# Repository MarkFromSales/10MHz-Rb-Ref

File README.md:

# 10MHz-Rb-Ref
Working on a custom controller for a 10MHz frequency reference

This sort of thing is fairly well documented in other places, but I wanted to use this as a way to learn. Most of my equipment has 10MHz frequency external reference capability and, although I don't really need it today, I'd like to learn more about the technology in general how it's used in instruments.

eBay often has 10MHz frequency references as components pulled out of telecom or similar equipment. After some quick searching I found that Rubidium is listed s one of the most stable and common references available. I bought an Efratom Rb 10MHz oscillator and this build log is to track efforts associated with getting it working.

I couldn't find much direct correlation between the device, its labels, and documentation. The FRS manual and pinouts accurately describe the device and its behavior, so I'm assuming I've got this correct so far :)

The connector that came with it was a pin type rather than solder cup. The heat from the soldering appeared to have weakened the pins resulting in some breakage on pin 1, causing issues with my testing.

Materials so far
* Efratom Rubidium Oscillator (eBay)
* ITT Cannon DAM11W1S connector (Digi-Key IDAM11W1S-ND)
* ITT Cannon DM53740-5008 coax pin (Digi-Key DM53740-5008PG-ND) - this turned out to be too small for my coax
* ITT Cannon DM53740-5002 coax pin (Digi-Key IDM53740-5002-ND)  - larger diameter on the coax side
* Amphenol 031-4803-RFX BNC panel adapter (Digi-Key ARF1685-ND)
* Amphenol 115101-01-06.00 BNC RG-316 cable in 6" length
* Mean Well IRM-60-24ST 24V 2.5A 60W AC-DC converter (Digi-Key 1866-3068-ND)

Efratom FRS Manual
https://s3.amazonaws.com/markfromsales/10mhzreference/Efratom_FRS_Manual.pdf

Efratom FRS Pinouts
https://s3.amazonaws.com/markfromsales/10mhzreference/Efratom_Pinouts.PNG

My unit's label
https://s3.amazonaws.com/markfromsales/10mhzreference/Efratom_Label.png

Screenshot of waveform (square, sort of)
https://s3.amazonaws.com/markfromsales/10mhzreference/Efratom_Waveform_20181114_1845.png

After reading through the documentation it looks like pins 1, 4, and 7 are not for customer use and there is some intersting items in the documentation. I connected them to my DAQ and ran a 60-minute capture from power-on to see what happened.

The documentation says that at power on the unit provides 10MHz via a crystal for about 4-minutes until the Rb lamp heats up. After the Rb lamp is heated it'll switch to Rb instead of crystal. This can be monitored by looking at the "Lock" pin 1 voltage; ~5V (mean is 5.1) is crystal and ~0V is Rb.

Check out the chart,
https://s3.amazonaws.com/markfromsales/10mhzreference/Efratom_Testing_Run_20181114_1840.PNG

It's very clear on my Siglent SDG 2042X counter function that the crystal is quite accurate and fairly stable, whereas the Rb is dead-on 10MHz and extremely stable.

Power draw is >1250mA while crystal is running and lamp is warming, drops down to 300-400mA after Rb locks. I was using Eevblog's uCurrent for this with a 3V battery. I've since soldered in an external battery connector and will use a 5V source from now on

Next steps:
* Re-run tests with a 5V power source in my uCurrent (3V current reading max is 1250mA) or run through DMM
* Package unit in metal box with appropriate PSU and cooling: Learn high-level thermal design principles
* Signal quality causes and does it matter? Learn high-level RF stuff and associated details
* Discover value of a frequency standard in my lab and projects

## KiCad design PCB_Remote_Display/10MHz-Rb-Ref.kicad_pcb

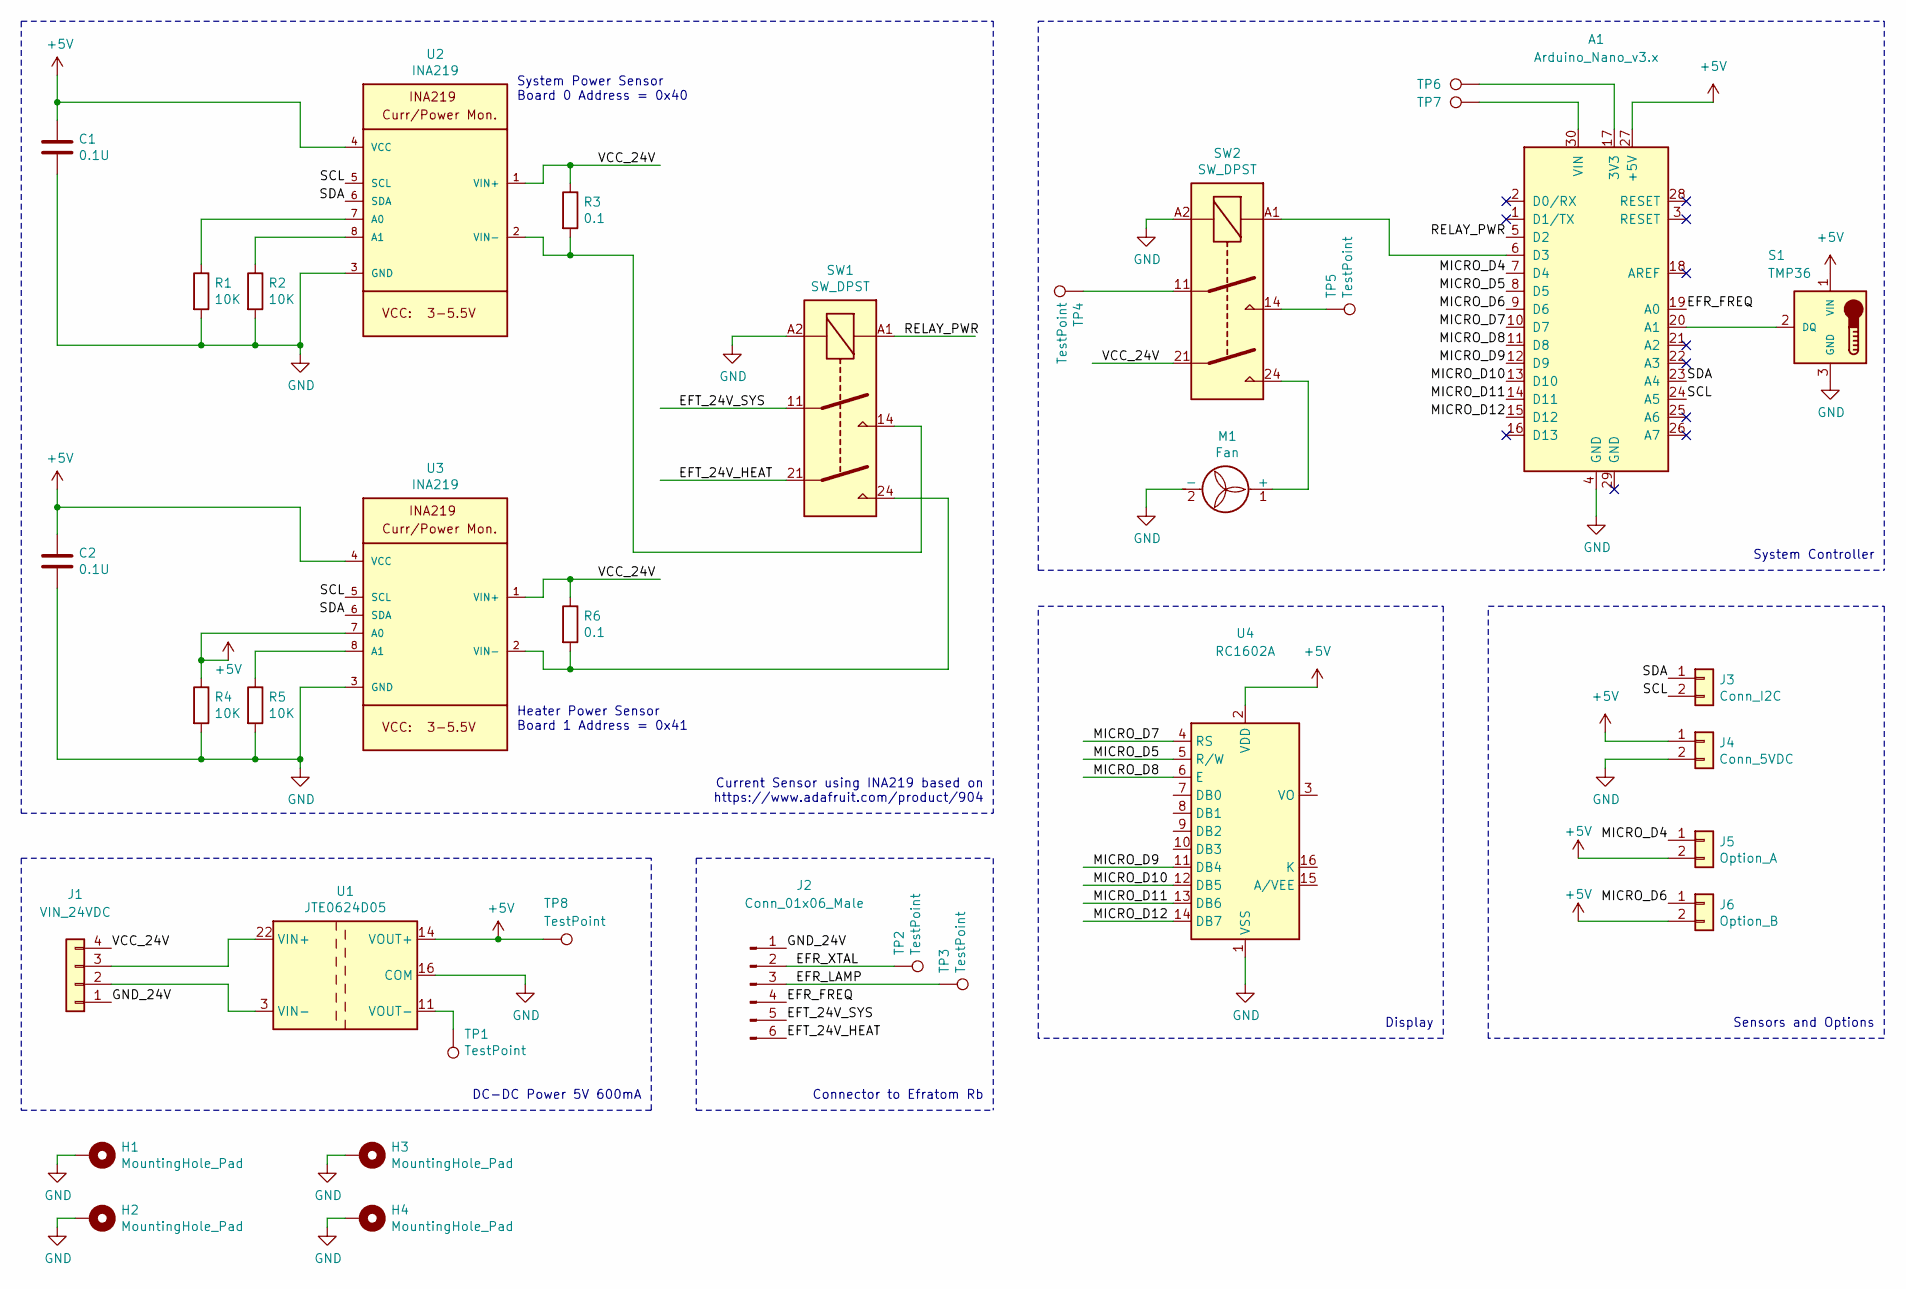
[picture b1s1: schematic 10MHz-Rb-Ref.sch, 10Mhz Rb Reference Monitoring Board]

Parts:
A1: Arduino_Nano_v3.x; Arduino_Nano
C1, C2: 0.1U; C_1206_3216Metric_Pad1.42x1.75mm_HandSolder
H1, H2, H3, H4: MountingHole_Pad; MountingHole_4.3mm_M4_Pad
J1: VIN_24VDC; JST_VH_B4P-VH-B_1x04_P3.96mm_Vertical
J2: Conn_01x06_Male; JST_VH_B6P-VH_1x06_P3.96mm_Vertical
J3: Conn_I2C; PinSocket_1x02_P2.54mm_Vertical
J4: Conn_5VDC; PinSocket_1x02_P2.54mm_Vertical
J5: Option_A; PinSocket_1x02_P2.54mm_Vertical
J6: Option_B; PinSocket_1x02_P2.54mm_Vertical
M1: Fan; JST_VH_B2P-VH-B_1x02_P3.96mm_Vertical
R1, R2, R4, R5: 10K; R_1206_3216Metric_Pad1.42x1.75mm_HandSolder
R3, R6: 0.1; R_2512_6332Metric_Pad1.52x3.35mm_HandSolder
S1: TMP36; TO-92_Inline
SW1, SW2: SW_DPST; Relay_DPST_Schrack-RT2-FormA_RM5mm
TP1, TP2, TP3, TP4, TP5, TP6, TP7, TP8: TestPoint; TestPoint_Pad_D1.5mm
U1: JTE0624D05; Converter_DCDC_XP_POWER_JTExxxxDxx_THT
U2, U3: INA219; SOT-23-8_Handsoldering
U4: RC1602A; PinSocket_2x08_P2.54mm_Vertical

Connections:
+5V: A1.27 (+5V), C1.1, C2.1, J4.1, J5.2, J6.2, R4.1, S1.1 (VIN), TP8.1, U1.14 (VOUT+), U2.4 (VCC), U3.4 (VCC), U3.7 (A0), U4.2 (VDD)
/EFR_FREQ: A1.19 (A0), J2.4
/EFR_LAMP: J2.3, TP3.1
/EFR_XTAL: J2.2, TP2.1
/EFT_24V_HEAT: J2.6, SW1.21
/EFT_24V_SYS: J2.5, SW1.11
/GND_24V: J1.1, J2.1
/MICRO_D4: A1.7 (D4), J5.1
/MICRO_D5: A1.8 (D5), U4.5 (R/W)
/MICRO_D6: A1.9 (D6), J6.1
/MICRO_D7: A1.10 (D7), U4.4 (RS)
/MICRO_D8: A1.11 (D8), U4.6 (E)
/MICRO_D9: A1.12 (D9), U4.11 (DB4)
/MICRO_D10: A1.13 (D10), U4.12 (DB5)
/MICRO_D11: A1.14 (D11), U4.13 (DB6)
/MICRO_D12: A1.15 (D12), U4.14 (DB7)
/RELAY_PWR: A1.5 (D2), SW1.A1
/SCL: A1.24 (A5), J3.2, U2.5 (SCL), U3.5 (SCL)
/SDA: A1.23 (A4), J3.1, U2.6 (SDA), U3.6 (SDA)
/VCC_24V: J1.4, R3.1, R6.1, SW2.21, U2.1 (VIN+), U3.1 (VIN+)
GND: A1.4 (GND), C1.2, C2.2, H1.1, H2.1, H3.1, H4.1, J4.2, M1.2 (-), R1.2, R2.2, R4.2, R5.2, S1.3 (GND), SW1.A2, SW2.A2, U1.9 (COM), U1.16 (COM), U2.3 (GND), U3.3 (GND), U4.1 (VSS)
unnamed: A1.6 (D3), SW2.A1
unnamed: A1.17 (3V3), TP6.1
unnamed: A1.20 (A1), S1.2 (DQ)
unnamed: A1.30 (VIN), TP7.1
unnamed: J1.2, U1.2 (VIN-), U1.3 (VIN-)
unnamed: J1.3, U1.22 (VIN+), U1.23 (VIN+)
unnamed: M1.1 (+), SW2.24
unnamed: R1.1, U2.7 (A0)
unnamed: R2.1, U2.8 (A1)
unnamed: R3.2, SW1.14, U2.2 (VIN-)
unnamed: R5.1, U3.8 (A1)
unnamed: R6.2, SW1.24, U3.2 (VIN-)
unnamed: SW2.11, TP4.1
unnamed: SW2.14, TP5.1
unnamed: TP1.1, U1.11 (VOUT-)

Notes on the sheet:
DC-DC Power 5V 600mA
Heater Power Sensor Board 1 Address = 0x41
System Power Sensor Board 0 Address = 0x40
Current Sensor using INA219 based on https://www.adafruit.com/product/904
Connector to Efratom Rb
System Controller
Display
Sensors and Options

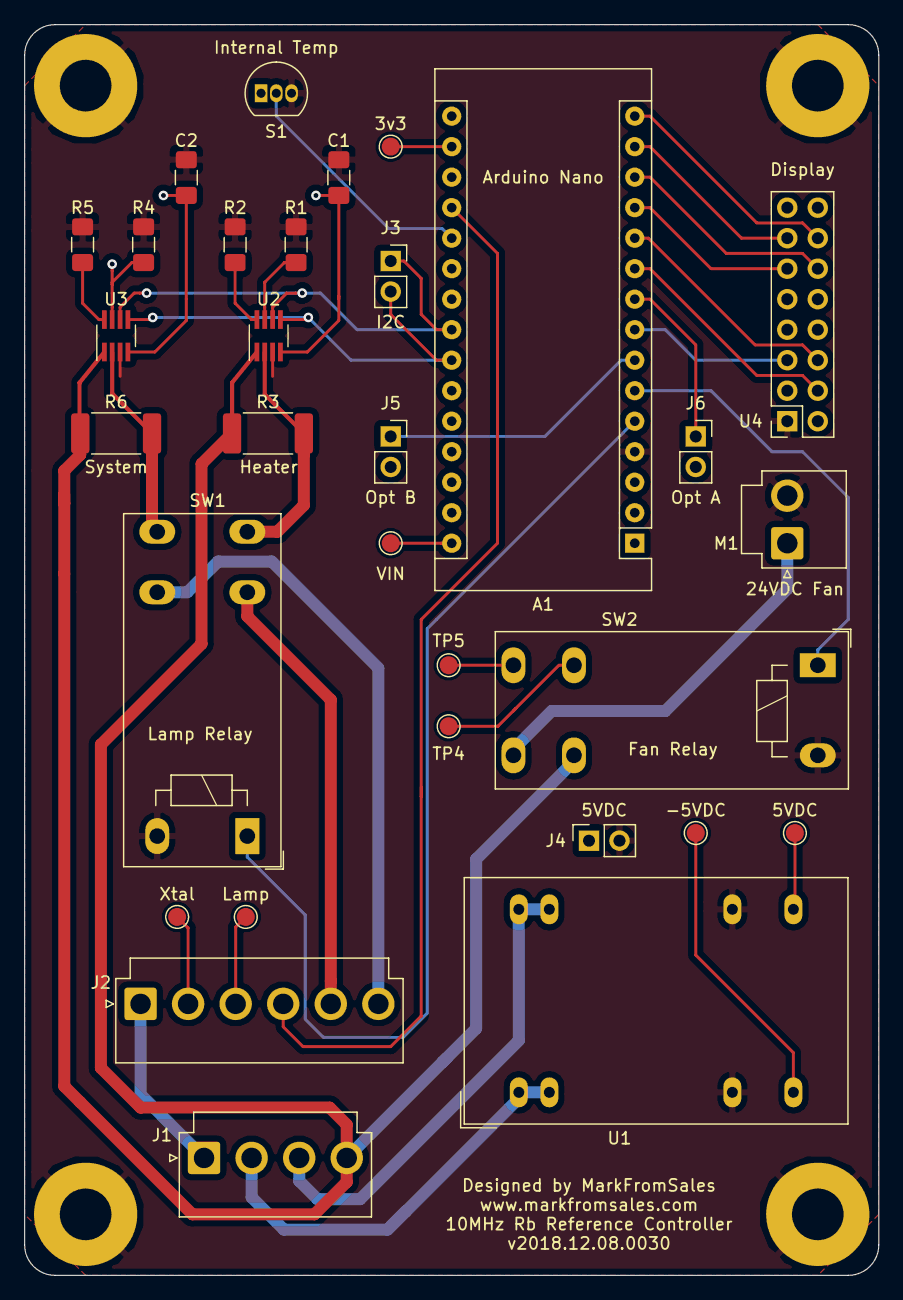
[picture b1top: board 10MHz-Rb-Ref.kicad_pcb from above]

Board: 2 copper layers, 71.1 x 104.1 mm, 35 parts (0 on the bottom side), 36 nets.

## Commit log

2019-02-02 Initial upload
2019-02-13 Updated structure
2019-03-19 Spring Break Edition
2019-03-19 Zipped up Gerbers
